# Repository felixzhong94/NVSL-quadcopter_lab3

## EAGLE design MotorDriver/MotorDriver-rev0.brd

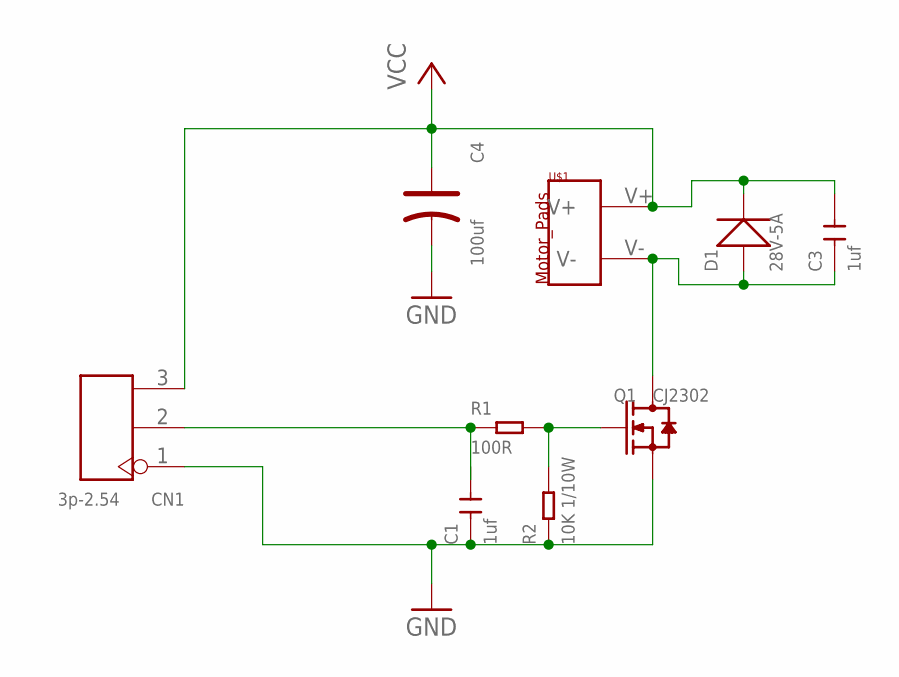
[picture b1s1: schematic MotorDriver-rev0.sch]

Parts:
C1: 1uf; C0402
C3: 1uf; C0603
C4: 100uf; AVX-B
CN1: 3p-2.54; H3-2.54
D1: 28V-5A; DO-214AA
Q1: CJ2302; SOT-23
R1: 100R; R0603
R2: 10K 1/10W; R0603
U$1: MOTOR_PADS

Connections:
GND: C1.1, C4.-, CN1.1, Q1.2 (S), R2.1
unnamed: CN1.2, R1.1
unnamed: Q1.1 (G), R1.2, R2.2
unnamed: C3.1, D1.+, Q1.3 (D), U$1.V-
VCC: C3.2, C4.+, CN1.3, D1.-, U$1.V+

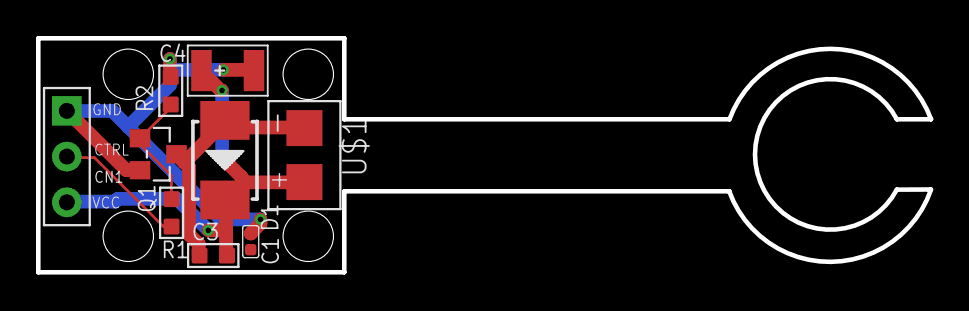
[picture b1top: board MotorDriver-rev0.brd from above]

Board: 2 copper layers, 49.6 x 13.0 mm, 9 parts (0 on the bottom side), 5 nets.

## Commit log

2016-03-17 Import from last year
2016-03-21 serial protocol code
2016-04-07 Adding Multiwii Skeleton
2016-04-07 Adding Multiwwi pde
2016-04-07 Adding LCD libraries for the LCD Display
2016-04-11 base lab done
